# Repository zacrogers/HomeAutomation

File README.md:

# HomeAutomation 

Project for various home automation nodes.
Node scraper python file contains classes for interacting with the nodes.

### Sensor Node
[Sensor Node Project Folder](SensorNode)

Gathers data from sensors and displays it via a web server.

Sensors
* Temperature 
* Light intensity
* Humidity

[Enclosure](https://cad.onshape.com/documents/5959c683fd64f6e6d8516b6b/w/ba91a7ba288052c9d6fa2683/e/a09c470a6dbf3c09050232f6)

### Power Node
[Power Node Project Folder](PowerNode)

Uses relays to control power outlets. Hosts a web server that can be used to turn the outlets on and off.

[Enclosure](https://cad.onshape.com/documents/b3409d9b9e3feabcd40a8fb0/w/2a3191f6e55cd64ce1e2338f/e/0e1e3c9eec61149ac09442c1)

### Android app
[App repository](https://github.com/zacrogers/HomeAutoApp)

Work in progress. Displays data from the sensor nodes and has buttons for controlling the power nodes.

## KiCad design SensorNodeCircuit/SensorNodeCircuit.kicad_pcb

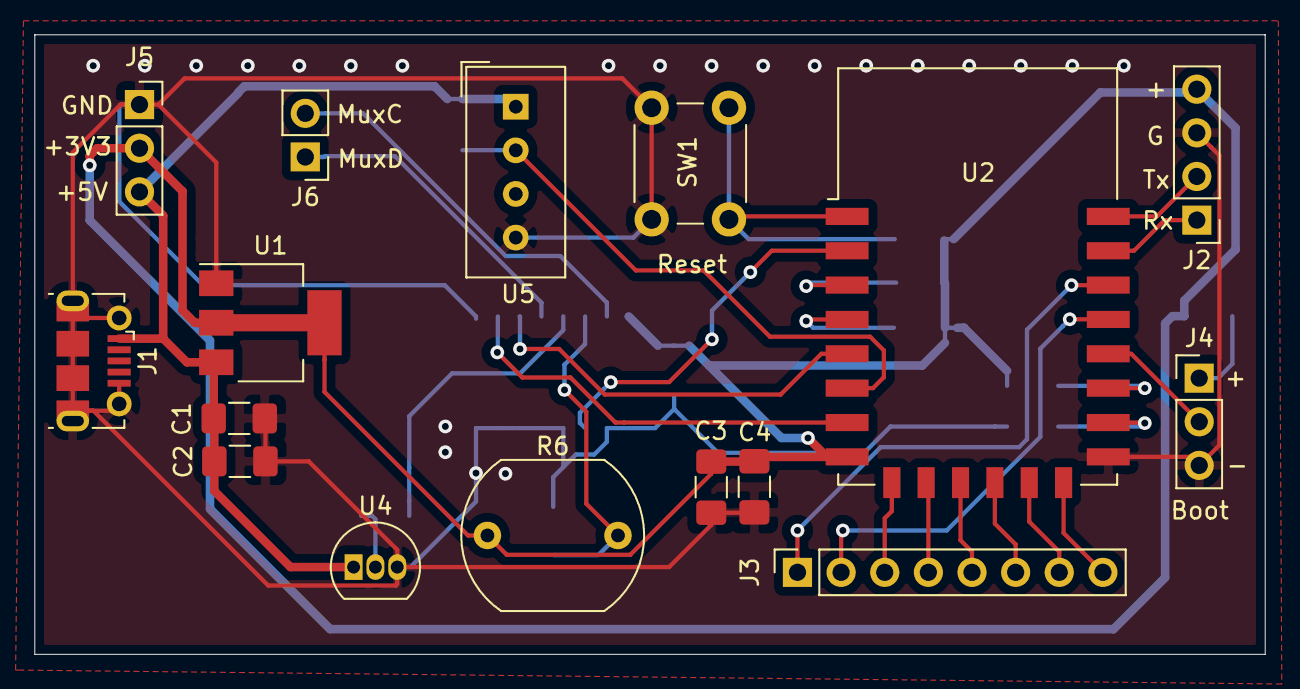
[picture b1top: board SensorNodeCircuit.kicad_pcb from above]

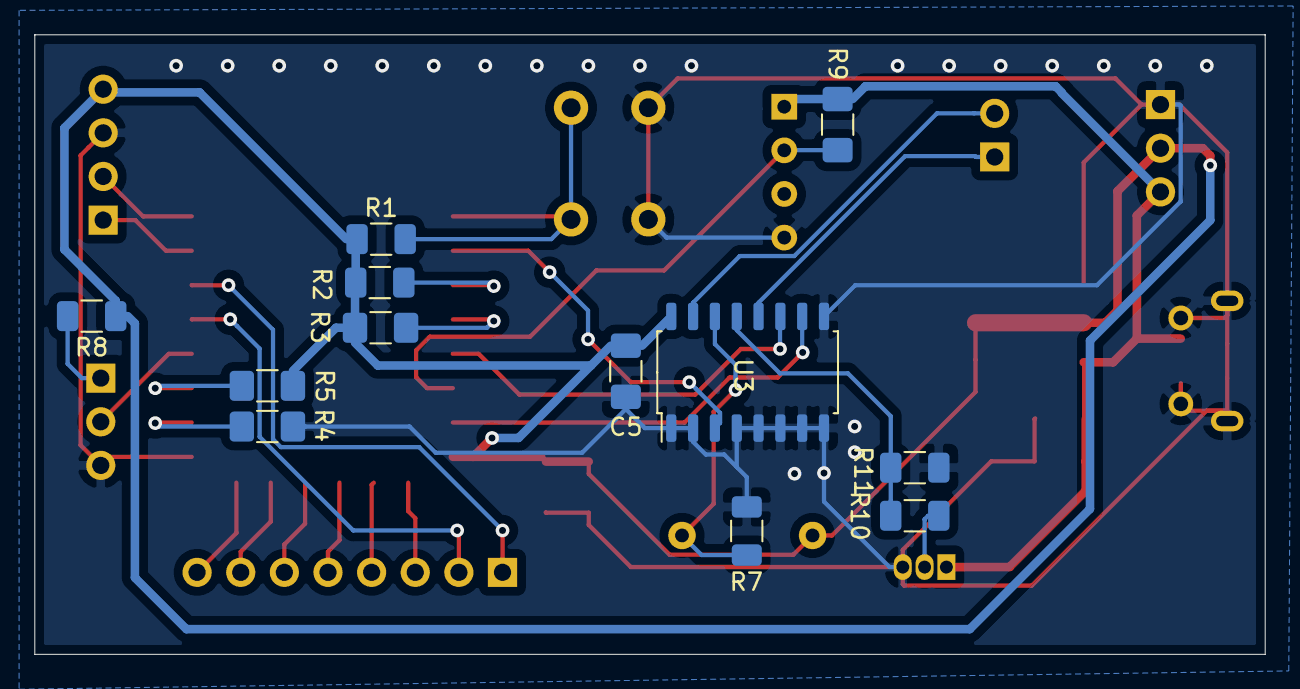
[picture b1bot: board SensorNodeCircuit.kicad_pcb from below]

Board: 2 copper layers, 71.6 x 36.1 mm, 28 parts (12 on the bottom side), 29 nets.

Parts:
C1, C2, C3, C4, C5: 0.1u; C_1206_3216Metric_Pad1.42x1.75mm_HandSolder
J1: USB_B_Micro; USB_Micro-B_Molex-105017-0001
J2: FTDI; PinHeader_1x04_P2.54mm_Vertical
J3: ExtraPins; PinSocket_1x08_P2.54mm_Vertical
J4: ProgJump; PinHeader_1x03_P2.54mm_Vertical
J5: PWR; PinSocket_1x03_P2.54mm_Vertical
J6: MuxExtra; PinHeader_1x02_P2.54mm_Vertical
R1, R2, R8, R10: 10k; R_1206_3216Metric
R3, R4, R5, R9: 10k; R_1206_3216Metric_Pad1.42x1.75mm_HandSolder
R6: LDR03; R_LDR_10x8.5mm_P7.6mm_Vertical
R7: 220r; R_1206_3216Metric
R11: 20k; R_1206_3216Metric
SW1: ResetButton; SW_PUSH_6mm_H8.5mm
U1: AMS1117-3.3; SOT-223-3_TabPin2
U2: ESP-12F; ESP-12E
U3: CD4051B; SOP-16_4.55x10.3mm_P1.27mm
U4: LM35-LP; TO-92_Inline
U5: DHT11; Aosong_DHT11_5.5x12.0_P2.54mm

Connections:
+3V3: C3.1, C4.1, C5.1, J2.4, J5.2, R1.1, R2.2, R3.2, R5.1, R6.1, R8.1, U1.2, U2.8, U3.16
+5V: C1.1, C2.1, J1.1, J5.3, R9.1, U1.3, U4.1, U5.1
ADC: U2.2, U3.3
CSO: J3.3, U2.9
DHTOut: R9.2, U2.6, U5.2
GND: C1.2, C2.2, C3.2, C4.2, C5.2, J1.5, J1.6, J2.3, J4.3, J5.1, R4.2, R7.2, R11.2, SW1.1, U1.1, U2.15, U3.1, U3.2, U3.4, U3.5, U3.6, U3.7, U3.8, U3.9, U4.3, U5.4
GPIO9: J3.5, U2.11
GPIO10: J3.6, U2.12
GPIO_0: J4.2, U2.18
LDROut: R6.2, R7.1, U3.14
MISO: J3.4, U2.10
MOSI: J3.7, U2.13
MuxA: U2.5, U3.11
MuxB: U2.7, U3.10
unnamed: J4.1, R8.2
unnamed: R2.1, U2.3
unnamed: R3.1, U2.4
unnamed: R4.1, U2.16
unnamed: R5.2, U2.17
unnamed: R10.2, U4.2
RST: R1.2, SW1.2, U2.1
RX: J2.1, U2.21
SCL: J3.1, U2.20
SCLK: J3.8, U2.14
SDA: J3.2, U2.19
SensorC: J6.2, U3.15
SensorD: J6.1, U3.12
TX: J2.2, U2.22
TempOut: R10.1, R11.1, U3.13

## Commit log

2020-12-14 Added sensor node
2020-12-15 Added python scraper for sensor data
2020-12-19 Added csv saving
2020-12-20 Added power node
2020-12-21 Added power node pages
2020-12-21 Added power node python class
2020-12-21 Added sensor node schematic
2020-12-21 Sensor Node schematic finished
2020-12-21 Updated pcb footprints
2020-12-21 Rough sensor node board layout done
2020-12-22 Fixed power node states changing
2020-12-22 Fixed up python PowerNode class`
2020-12-22 Added docstrings to PowerNode
2020-12-22 Finished sensor node pcb layout
2020-12-22 Generated gerbers
2020-12-22 Added display labels to power node
2020-12-22 Assigned pins to power node
2020-12-23 Formatting
2020-12-28 Swapped on/off logic levels
2021-01-02 Added sensor circuit v2
2021-01-02 Tidied up pcb
2021-01-05 Added sensornode pcb 3d render
2021-01-13 Added link to sensor node enclosure
2021-01-16 Sensor node pcb updated
    Added voltage divider to temp sensor output, and thicker power traces
2021-01-16 Fixed pin assignments for sensor node
    Pin assignment were changed to match pcb pin mapping
2021-01-17 Added sensor node enclosure files
2021-01-18 Added wifi manager
2021-01-18 Fixed humidity reading
2021-01-23 Fixed dht double definition
2021-01-27 Added motorised lock project
2021-01-27 Motorised lock servo control added
2021-01-30 Added access card function protos
2021-02-05 Added access feedback functions
2021-06-16 Changed to use mqtt
2021-06-16 Added stl parts
2021-06-19 Added SensorNodeV2 & updated lock
2021-06-21 Almost finished wifi
